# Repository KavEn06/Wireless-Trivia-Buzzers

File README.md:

# Wireless-Trivia-Buzzers
### What is it?
There will be four buzzer boxes and one main box. Each buzzer box will represent a team (Teams A, B, C, and D) and will have four buttons, one for each player. The main box will house a screen that allows the host to see which player buzzed in first and will also include a reset button to clear all buzzes. For the time being, I plan to include two modes. The first mode allows only one player per team to buzz in, any player from the team can buzz, but only the first buzz from that team will register. The second mode is a free-for-all, where all 16 players can buzz in individually, regardless of their team.

### Backstory 
Basically this idea came to me while me and a couple of friends were practicing for a trivia competition that my school's Classics club hosts semi-annually (with other neighboring schools). I realised that many other schools didn't have the funds to buy the "official" buzzers that all the other schools use, which means that they just end up using some horrible online version, which are very dependent on how good your wifi is. Moreover, these buzzers we're SO HEAVY and annoying to set up that half the time my friends and I didn't even bother practicing because we were too lazy to set up the buzzers and get an actual competition environment going. 

## Architecture & Features 
### Hardware
- **Display:** 16x2 LCD With an I2C Module
- **Chip:** ESP32
- **Audio:**
  - **DAC:** MAX98357A
  - **Speakers:** 2W Speakers
- **Power:** 9V Battery or USB-C 

## Pictures 
### 3D Model 

### Wiring Diagram

### PCBs 
Buzzer Box 

Main Box 

## BOM 
| Item                          | Purpose  | Source | Price  | Inventory          |
|-------------------------------|----------|--------|--------|--------------------|
| 5x ESP32 (38 Pin) Dev Board   | Controller | [Link](https://www.aliexpress.us/item/3256806817804530.html) | $32.10 | Owned              |
| 16x2 LCD with I2C Module      | Output   | [Link](https://www.aliexpress.us/item/3256806005226729.html) | $3.47  | Owned              |
| Speakers                      | Output   | [Link](https://www.aliexpress.us/item/3256806149654655.html) | $2.99  | Owned              |
| 5 LEDS                        | Output   | [Link](https://lcsc.com/product-detail/LED-Indication-Discrete_Everlight-Elec-204-10SURD-S530-A3_C99772.html) | $0.50  | Owned              |
| MAX98357A                     | Output   | [Link](https://www.aliexpress.us/item/3256806882501015.html) | $2.53  | Owned              |
| 17x Push Buttons              | Input    | [Link](https://www.aliexpress.us/item/4000097252595.html)    | $10.25 | Owned              |
| 16x Charger Wires (Any work)  | Input    | [Link](https://www.aliexpress.us/item/3256806607225846.html) | $14.43 | Owned              |
| Micro SD Card Module          | Input    | [Link](https://www.aliexpress.us/item/3256806271288304.html) | $1.28  | Highway Provided   |
| 5x USB-C Port                 | Input    | [Link](https://www.aliexpress.us/item/3256805808963500.html) | $4.11  | Owned              |
| 5x 9V Battery                 | Power    | [Link](https://www.amazon.com/dp/B00MH4QM1S)                 | $12.69 | Highway Provided   |
| 5x 9V Battery Connector       | Power    | [Link](https://lcsc.com/product-detail/Battery-Holders-Clips-Contacts_Q-J-C70374_C70374.html) | $0.51  | Owned              |
| 5x DC - DC Buck Converter     | Power    | [Link](https://www.aliexpress.us/item/3256807145249780.html) | $4.65  | Highway Provided   |
| 5x 3 Way (SPDT) Switch        | Switch   | [Link](https://lcsc.com/product-detail/slide-switches_usakro-ss-12f15-g6_C698214.html) | $0.41  | Highway Provided   |
| 2.54mm Headers                | Connector| [Link](https://lcsc.com/product-detail/Female-Headers_Megastar-ZX-PM2-54-1-15PY_C7499333.html) | $0.84  | Highway Provided   |
| Buzzer Box PCB (w/ Shipping) | PCB      | JLCPCB | $10.00 | Highway Provided   |
| Main Box PCB (w/ Shipping)   | PCB      | JLCPCB | $5.00  | Highway Provided   |
|                               |          | Total: | $105.76|                    |
|                               |          | Total (Highway Provided): | $34.87 |         |

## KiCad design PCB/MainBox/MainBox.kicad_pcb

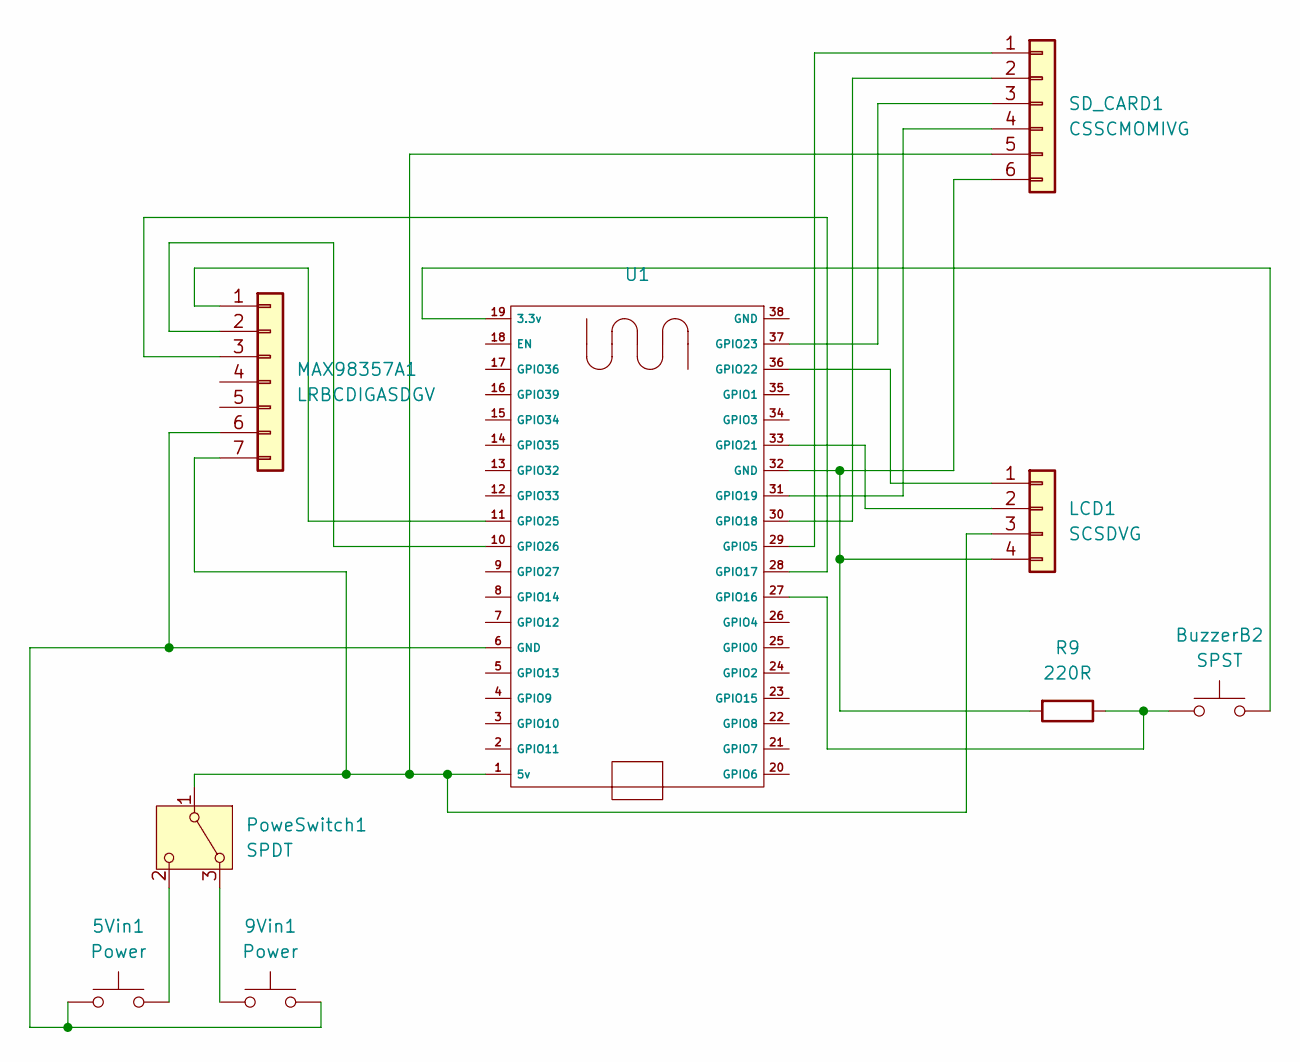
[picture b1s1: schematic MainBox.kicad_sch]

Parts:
5Vin1, 9Vin1: Power; SW_PUSH_1P1T_6x3.5mm_H4.3_APEM_MJTP1243
BuzzerB2: SPST; SW_PUSH_1P1T_6x3.5mm_H4.3_APEM_MJTP1243
LCD1: SCSDVG; PinSocket_1x04_P2.54mm_Vertical
MAX98357A1: LRBCDIGASDGV; MAX98357A
PoweSwitch1: SPDT; SW_Slide-03_Wuerth-WS-SLTV_10x2.5x6.4_P2.54mm
R9: 220R; R_Axial_DIN0204_L3.6mm_D1.6mm_P7.62mm_Horizontal
SD_CARD1: CSSCMOMIVG; Micro SD Card Module
U1: ESP32_38pin

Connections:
unnamed: LCD1.1, U1.36 (GPIO22)
unnamed: LCD1.2, U1.33 (GPIO21)
unnamed: LCD1.3, MAX98357A1.7, PoweSwitch1.1 (B), SD_CARD1.5, U1.1 (5v)
unnamed: LCD1.4, R9.2, SD_CARD1.6, U1.32 (GND)
unnamed: MAX98357A1.1, U1.11 (GPIO25)
unnamed: MAX98357A1.2, U1.10 (GPIO26)
unnamed: MAX98357A1.3, U1.28 (GPIO17)
unnamed: 5Vin1.1, 9Vin1.1, MAX98357A1.6, U1.6 (GND)
unnamed: 9Vin1.2, PoweSwitch1.3 (A)
unnamed: 5Vin1.2, PoweSwitch1.2 (C)
unnamed: SD_CARD1.1, U1.29 (GPIO5)
unnamed: SD_CARD1.2, U1.30 (GPIO18)
unnamed: SD_CARD1.3, U1.37 (GPIO23)
unnamed: SD_CARD1.4, U1.31 (GPIO19)
unnamed: BuzzerB2.2, U1.19 (3.3v)
unnamed: BuzzerB2.1, R9.1, U1.27 (GPIO16)

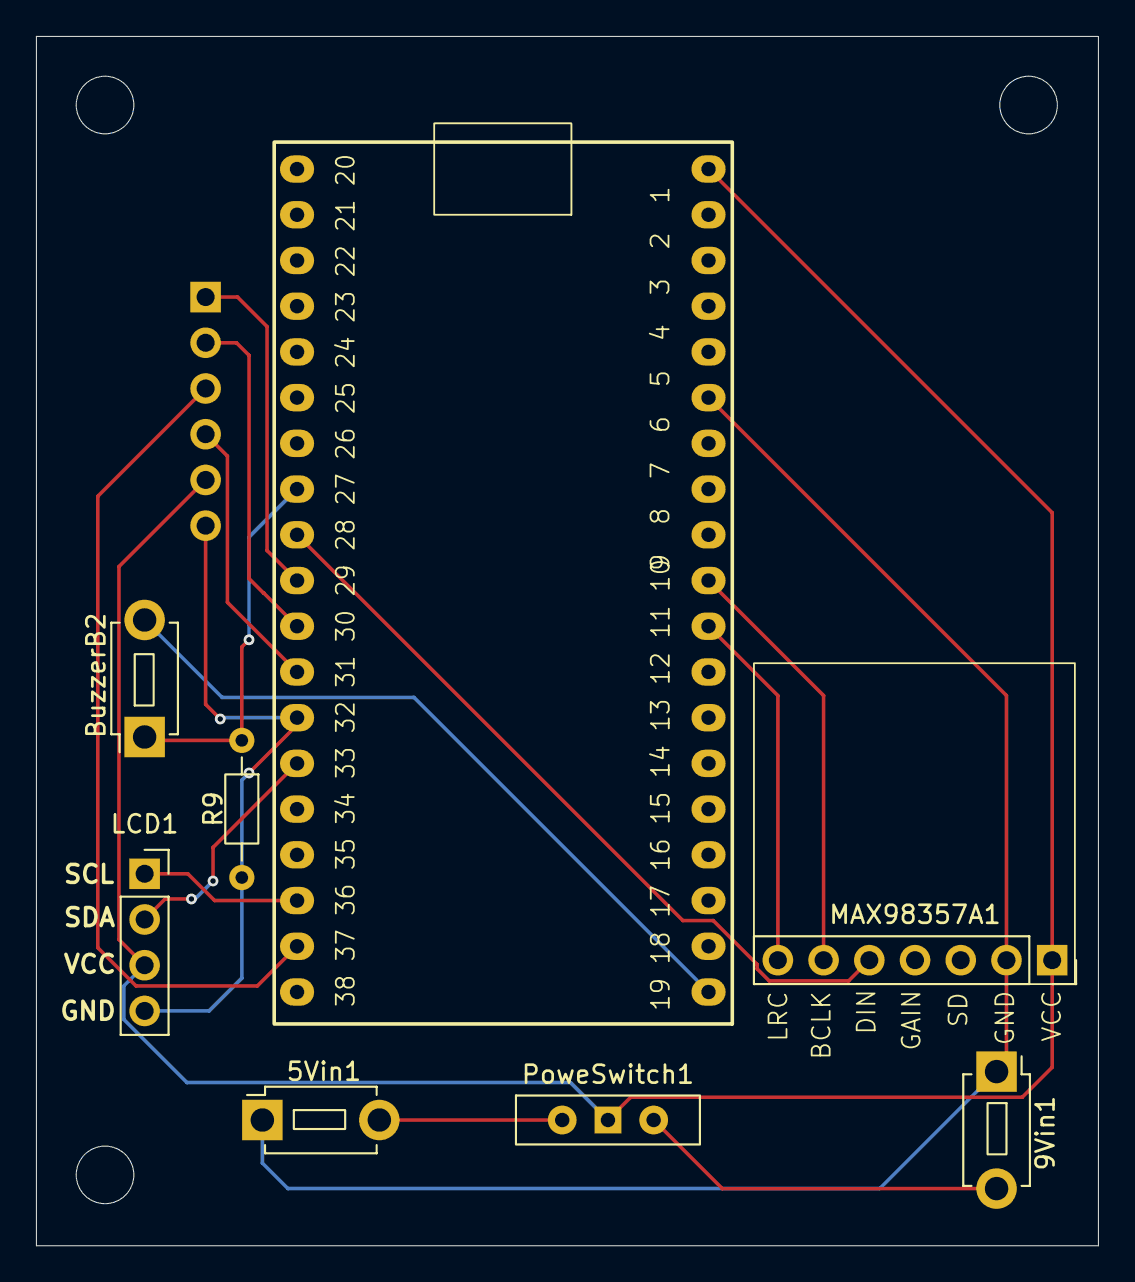
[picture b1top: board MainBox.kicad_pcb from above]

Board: 2 copper layers, 59.0 x 67.2 mm, 9 parts (1 on the bottom side), 16 nets.

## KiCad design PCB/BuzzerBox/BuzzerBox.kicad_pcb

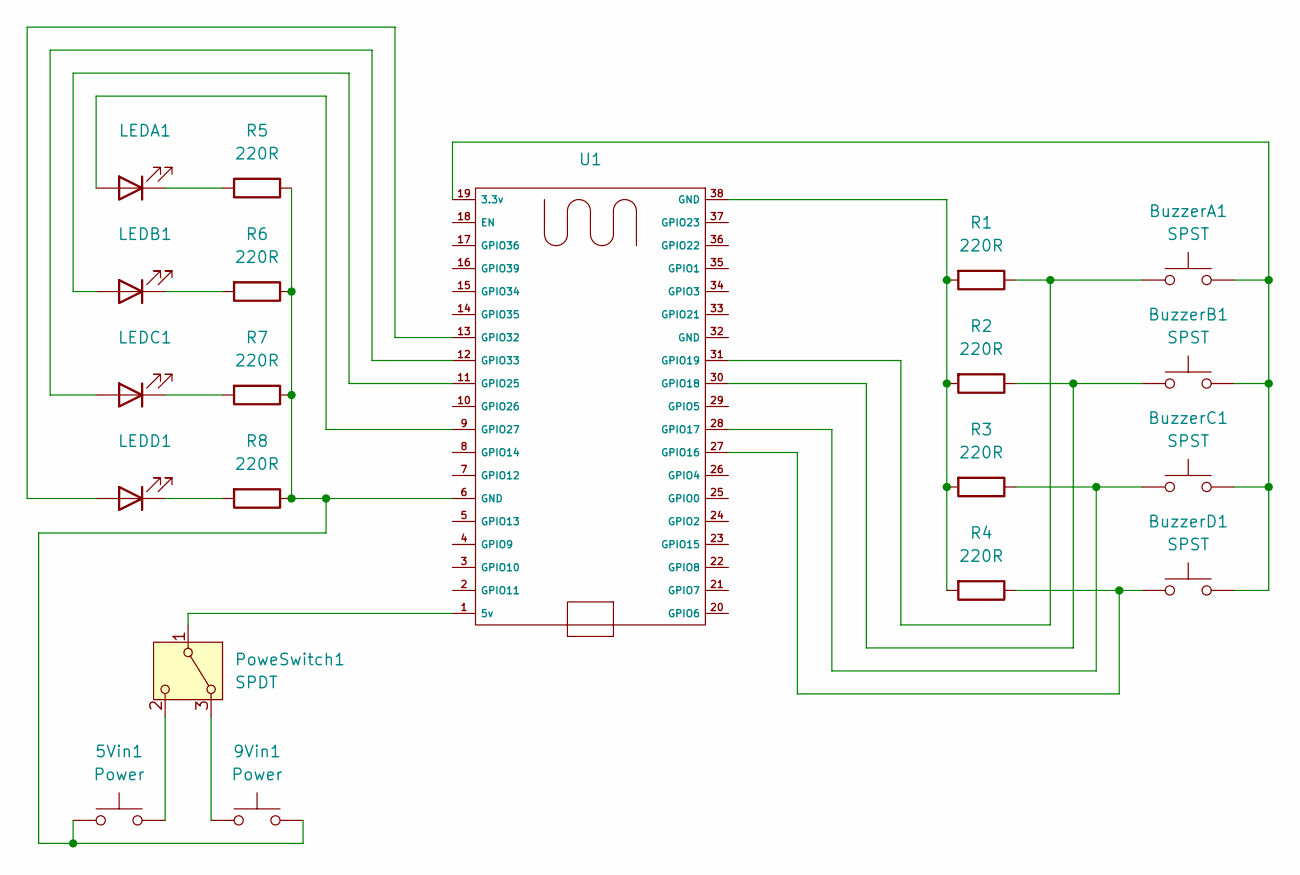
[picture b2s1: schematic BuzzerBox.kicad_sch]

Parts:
5Vin1, 9Vin1: Power; SW_PUSH_1P1T_6x3.5mm_H4.3_APEM_MJTP1243
BuzzerA1: SPST; SW_PUSH_1P1T_6x3.5mm_H4.3_APEM_MJTP1243
BuzzerB1: SPST; SW_PUSH_1P1T_6x3.5mm_H4.3_APEM_MJTP1243
BuzzerC1: SPST; SW_PUSH_1P1T_6x3.5mm_H4.3_APEM_MJTP1243
BuzzerD1: SPST; SW_PUSH_1P1T_6x3.5mm_H4.3_APEM_MJTP1243
LEDA1: LED_D5.0mm
LEDB1: LED_D5.0mm
LEDC1: LED_D5.0mm
LEDD1: LED_D5.0mm
PoweSwitch1: SPDT; SW_Slide-03_Wuerth-WS-SLTV_10x2.5x6.4_P2.54mm
R1, R2, R3, R4, R5, R6, R7, R8: 220R; R_0805_2012Metric; LCSC C17557
U1: ESP32_38pin

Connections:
unnamed: 5Vin1.1, 9Vin1.1, R5.1, R6.1, R7.1, R8.1, U1.6 (GND)
unnamed: LEDA1.2 (A), U1.9 (GPIO27)
unnamed: LEDA1.1 (K), R5.2
unnamed: LEDB1.2 (A), U1.11 (GPIO25)
unnamed: LEDB1.1 (K), R6.2
unnamed: LEDC1.2 (A), U1.12 (GPIO33)
unnamed: LEDC1.1 (K), R7.2
unnamed: LEDD1.2 (A), U1.13 (GPIO32)
unnamed: LEDD1.1 (K), R8.2
unnamed: 9Vin1.2, PoweSwitch1.3 (A)
unnamed: PoweSwitch1.1 (B), U1.1 (5v)
unnamed: 5Vin1.2, PoweSwitch1.2 (C)
unnamed: R1.2, R2.2, R3.2, R4.2, U1.38 (GND)
unnamed: BuzzerA1.2, BuzzerB1.2, BuzzerC1.2, BuzzerD1.2, U1.19 (3.3v)
unnamed: BuzzerD1.1, R4.1, U1.27 (GPIO16)
unnamed: BuzzerC1.1, R3.1, U1.28 (GPIO17)
unnamed: BuzzerB1.1, R2.1, U1.30 (GPIO18)
unnamed: BuzzerA1.1, R1.1, U1.31 (GPIO19)

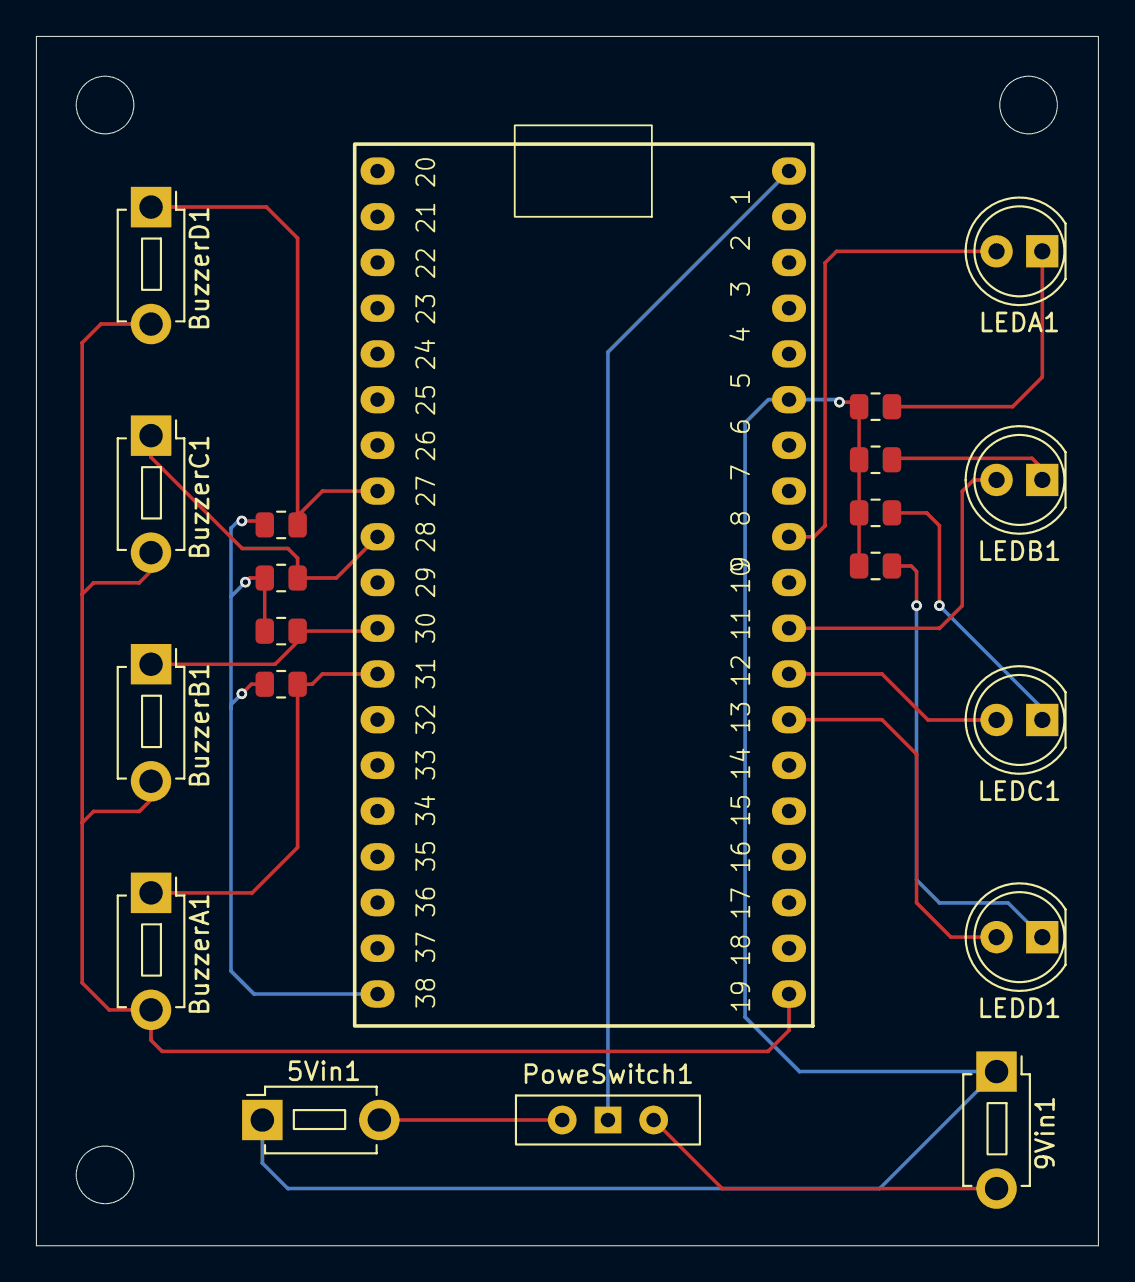
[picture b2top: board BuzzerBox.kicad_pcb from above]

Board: 2 copper layers, 59.0 x 67.2 mm, 20 parts (0 on the bottom side), 18 nets.

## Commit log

2025-05-27 Make PCB Folder
2025-05-27 Buzzer Box PCB
2025-06-04 Create a
2025-06-04 PCB Files
